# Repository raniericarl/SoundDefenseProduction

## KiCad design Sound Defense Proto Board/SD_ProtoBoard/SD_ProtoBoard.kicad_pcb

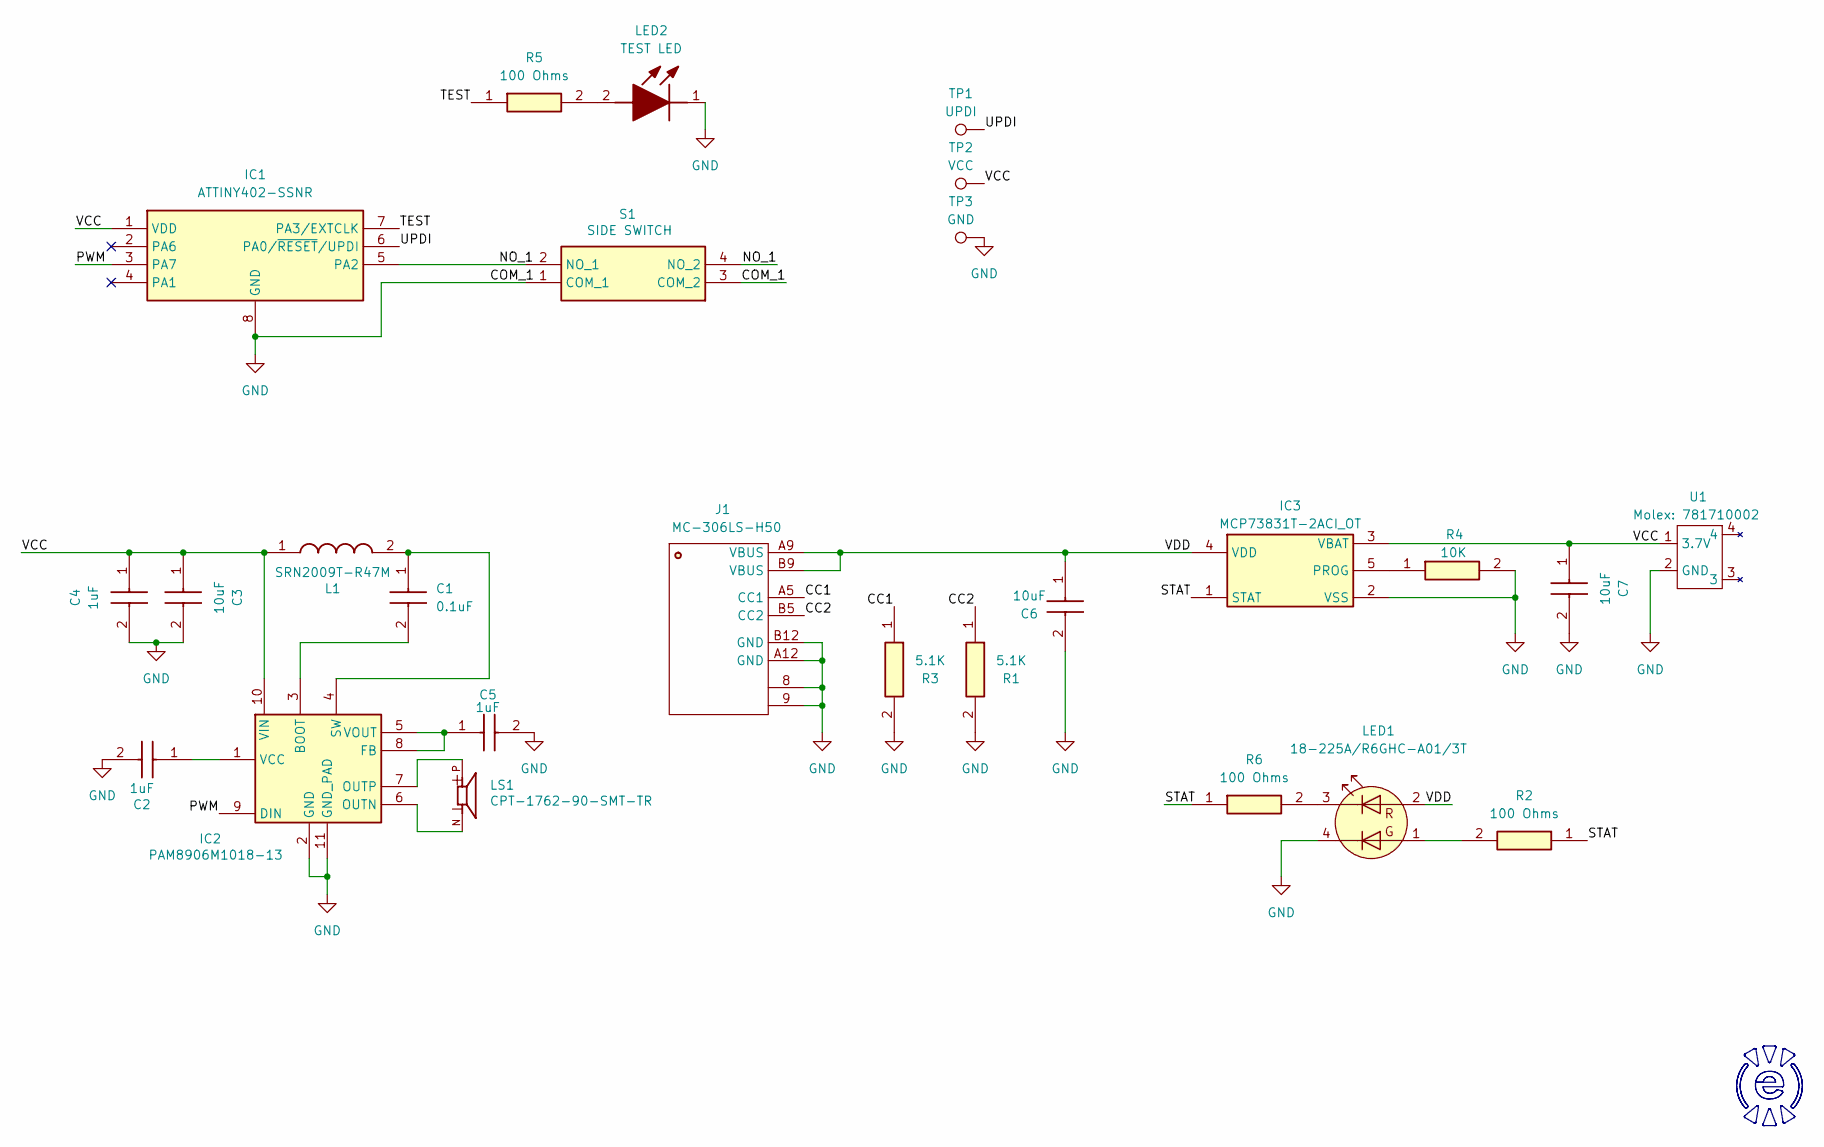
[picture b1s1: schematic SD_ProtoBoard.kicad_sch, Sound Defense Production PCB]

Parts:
C1: 0.1uF; CAPC1005X55N; Manufacturer_Part_Number 0402B104K160CT; Mouser Part Number 791-0402B104K160CT
C2, C4, C5: 1uF; CAPC1005X55N; Manufacturer_Part_Number GRM155R61E105KA12D; Mouser Part Number 81-GRM155R61E105KA2D
C3, C6, C7: 10uF; CAPC1608X90N; Manufacturer_Part_Number GRM188R61E106MA73D; Mouser Part Number 81-GRM188R61E106MA3D
IC1: ATTINY402-SSNR; SOIC127P600X175-8N; Manufacturer_Part_Number ATTINY402-SSNR; Mouser Part Number 579-ATTINY402-SSNR
IC2: PAM8906M1018-13; SOP50P490X110-10N; Manufacturer_Part_Number PAM8906M1018-13; Mouser Part Number 621-PAM8906M1018-13
IC3: MCP73831T-2ACI_OT; SOT95P270X145-5N; Manufacturer_Part_Number MCP73831T-2ACI/OT; Mouser Part Number 579-MCP73831T-2ACIOT
J1: MC-306LS-H50
L1: SRN2009T-R47M; INDC2016X95N; Manufacturer_Part_Number SRN2009T-R47M; Mouser Part Number 652-SRN2009T-R47M
LED1: 18-225A/R6GHC-A01/3T; 18-225A R6GHC-A01 3T
LED2: TEST LED; LEDC1608X80N; Manufacturer_Part_Number 150060VS75000; Mouser Part Number 710-150060VS75000
LS1: CPT-1762-90-SMT-TR; XDCR_CPT-1762-90-SMT-TR; PARTREV 1.01
R1, R3: 5.1K; RESC1005X40N; Manufacturer_Part_Number 0402WGF5101TCE
R2, R5, R6: 100 Ohms; RESC1005X40N; Manufacturer_Part_Number RC0402FR-07100RL; Mouser Part Number 603-RC0402FR-07100RL
R4: 10K; RESC1005X40N; Manufacturer_Part_Number 0402WGF1002TCE
S1: SIDE SWITCH; 436331045822; Manufacturer_Part_Number 436331045822; Mouser Part Number 710-436331045822
TP1: UPDI; TestPoint_Pad_2.5x2.5mm
TP2: VCC; TestPoint_Pad_2.5x2.5mm
TP3: GND; TestPoint_Pad_3.0x3.0mm
U1: Molex: 781710002; CONN02_781710002_MOL

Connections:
/CC1: J1.A5 (CC1), R3.1
/CC2: J1.B5 (CC2), R1.1
/NO_1: IC1.5 (PA2), S1.2 (NO_1), S1.4 (NO_2)
/PWM: IC1.3 (PA7), IC2.9 (DIN)
/STAT: IC3.1 (STAT), R2.1, R6.1
/TEST: IC1.7 (PA3/EXTCLK), R5.1
/UPDI: IC1.6 (PA0/~RESET/UPDI), TP1.1
/VCC: C3.1, C4.1, C7.1, IC1.1 (VDD), IC2.10 (VIN), IC3.3 (VBAT), L1.1, TP2.1, U1.1 (3.7V)
/VDD: C6.1, IC3.4 (VDD), J1.A9 (VBUS), J1.B9 (VBUS), LED1.2 (A1)
GND: C2.2, C3.2, C4.2, C5.2, C6.2, C7.2, IC1.8 (GND), IC2.2 (GND), IC2.11 (GND_PAD), IC3.2 (VSS), J1.8, J1.9, J1.A12 (GND), J1.B12 (GND), LED1.4 (K2), LED2.1 (K), R1.2, R3.2, R4.2, S1.1 (COM_1), S1.3 (COM_2), TP3.1, U1.2 (GND)
unnamed: C1.2, IC2.3 (BOOT)
unnamed: C5.1, IC2.5 (VOUT), IC2.8 (FB)
unnamed: IC2.6 (OUTN), LS1.N
unnamed: IC2.7 (OUTP), LS1.P
unnamed: C1.1, IC2.4 (SW), L1.2
unnamed: C2.1, IC2.1 (VCC)
unnamed: IC3.5 (PROG), R4.1
unnamed: LED1.1 (A2), R2.2
unnamed: LED1.3 (K1), R6.2
unnamed: LED2.2 (A), R5.2

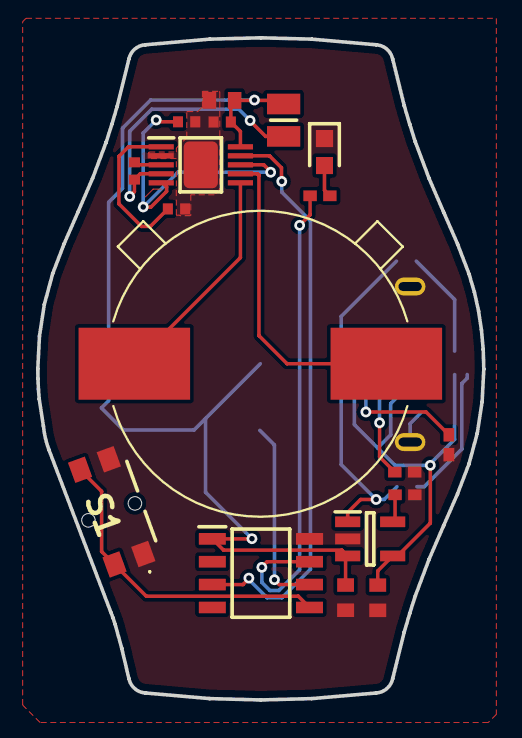
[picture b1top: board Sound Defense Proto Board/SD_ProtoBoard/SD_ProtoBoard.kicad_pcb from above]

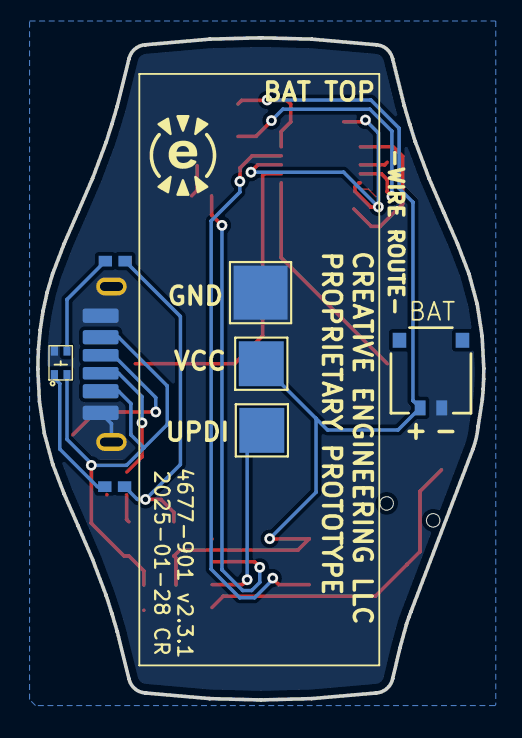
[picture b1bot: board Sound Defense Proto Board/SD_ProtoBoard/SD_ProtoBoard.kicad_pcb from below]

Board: 2 copper layers, 24.8 x 36.8 mm, 26 parts (8 on the bottom side), 20 nets.

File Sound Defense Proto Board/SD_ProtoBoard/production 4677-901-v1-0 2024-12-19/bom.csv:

Designator,Footprint,Quantity,Value,LCSC Part #
C1,CAPC1005X55N,1,0.1uF,
"C2, C4, C5",CAPC1005X55N,3,1uF,
"C3, C6, C7",CAPC1608X90N,3,10uF,
IC1,SOIC127P600X175-8N,1,ATTINY402-SSNR,
IC2,SOP50P490X110-10N,1,PAM8906M1018-13,
IC3,SOT95P270X145-5N,1,MCP73831T-2ACI_OT,
J1,MC-306LS-H50,1,MC-306LS-H50,
L1,INDC2016X95N,1,SRN2009T-R47M,
LED1,LEDC1608X80N,1,CHARGE INDICATOR,
LS1,XDCR_CPT-1762-90-SMT-TR,1,CPT-1762-90-SMT-TR,
"R1, R3",RESC1005X40N,2,5.1K,
R2,RESC1005X40N,1,100 Ohms,
R4,RESC1005X40N,1,10K,
S1,436331045822,1,SIDE SWITCH,
TP1,TestPoint_Pad_2.5x2.5mm,1,UPDI,
TP2,TestPoint_Pad_2.5x2.5mm,1,VCC,
TP3,TestPoint_Pad_3.0x3.0mm,1,GND,
U1,LP402025,1,LP401230,

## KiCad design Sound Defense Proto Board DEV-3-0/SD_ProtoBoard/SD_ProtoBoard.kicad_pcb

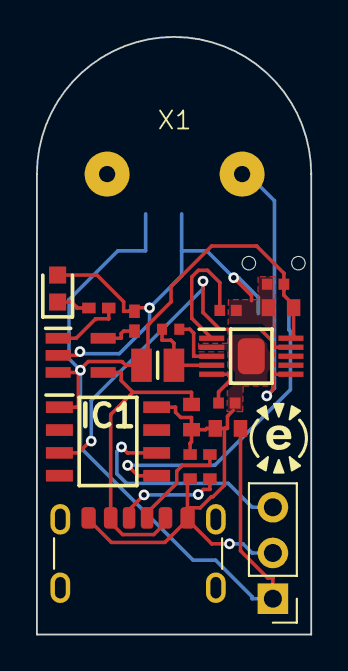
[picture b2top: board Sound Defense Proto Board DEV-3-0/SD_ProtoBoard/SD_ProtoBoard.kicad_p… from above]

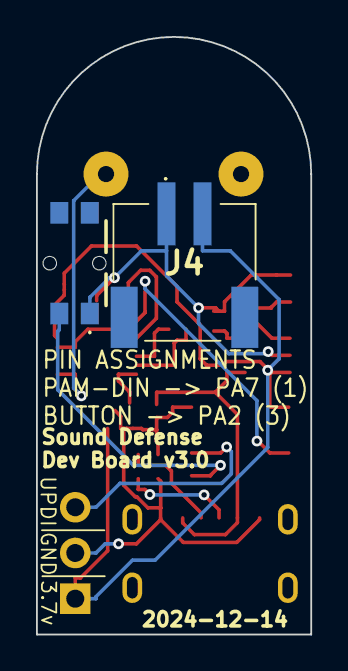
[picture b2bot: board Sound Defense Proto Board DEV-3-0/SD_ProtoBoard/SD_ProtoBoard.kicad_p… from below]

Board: 2 copper layers, 15.2 x 33.2 mm, 21 parts (2 on the bottom side), 17 nets.

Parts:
C1: 0.1uF 0402B104K160CT; CAPC1005X55N
C2, C4, C5: 1uF GRM155R61E105KA12D; CAPC1005X55N
C3, C6, C7: 10uF GRM188R61E106MA73D; CAPC1608X90N
IC1: ATTINY402-SSNR; SOIC127P600X175-8N
IC2: PAM8906M1018-13; SOP50P490X110-10N
IC3: MCP73831T-2ACI_OT; SOT95P270X145-5N
J1: Conn_01x03_Pin; PinHeader_1x03_P2.54mm_Vertical
J3: USB_C_Receptacle_PowerOnly_6P; USB_C_Receptacle_GCT_USB4125-xx-x-0190_6P_TopMnt_Horizontal
J4: S2B-PH-SM4-TB_LF__SN_; S2BPHSM4TBLFSN
L1: SRN2009T-R47M; INDC2016X95N
LED1: 150060VS75000; LEDC1608X80N
R1, R3: 5.1KOhm; RESC1005X40N
R2: 100 Ohms; RESC1005X40N
R4: 10K Ohm; RESC1005X40N
S1: 436331045822
X1: CPT-1404-85T; SD-CPT-1404-85T

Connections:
/UPDI: IC1.6 (PA0/~RESET/UPDI), J1.3
/VBAT: C3.1, C4.1, C7.1, IC1.1 (VDD), IC2.10 (VIN), IC3.3 (VBAT), J1.1, J4.2, L1.1
GND: C2.1, C3.2, C4.2, C5.2, C6.1, C7.2, IC1.8 (GND), IC2.2 (GND), IC2.11 (GND_PAD), IC3.2 (VSS), J1.2, J3.A12 (GND), J3.B12 (GND), J4.1, LED1.2 (A), R1.1, R3.1, R4.2, S1.1 (COM_1)
unnamed: IC1.5 (PA2), S1.2 (NO_1)
unnamed: IC1.3 (PA7), IC2.9 (DIN)
unnamed: C1.2, IC2.3 (BOOT)
unnamed: C2.2, IC2.5 (VOUT), IC2.8 (FB)
unnamed: IC2.6 (OUTN), X1.2
unnamed: IC2.7 (OUTP), X1.1
unnamed: C1.1, IC2.4 (SW), L1.2
unnamed: C5.1, IC2.1 (VCC)
unnamed: IC3.5 (PROG), R4.1
unnamed: IC3.1 (STAT), R2.2
unnamed: C6.2, IC3.4 (VDD), J3.A9 (VBUS), J3.B9 (VBUS)
unnamed: J3.A5 (CC1), R1.2
unnamed: J3.B5 (CC2), R3.2
unnamed: LED1.1 (K), R2.1

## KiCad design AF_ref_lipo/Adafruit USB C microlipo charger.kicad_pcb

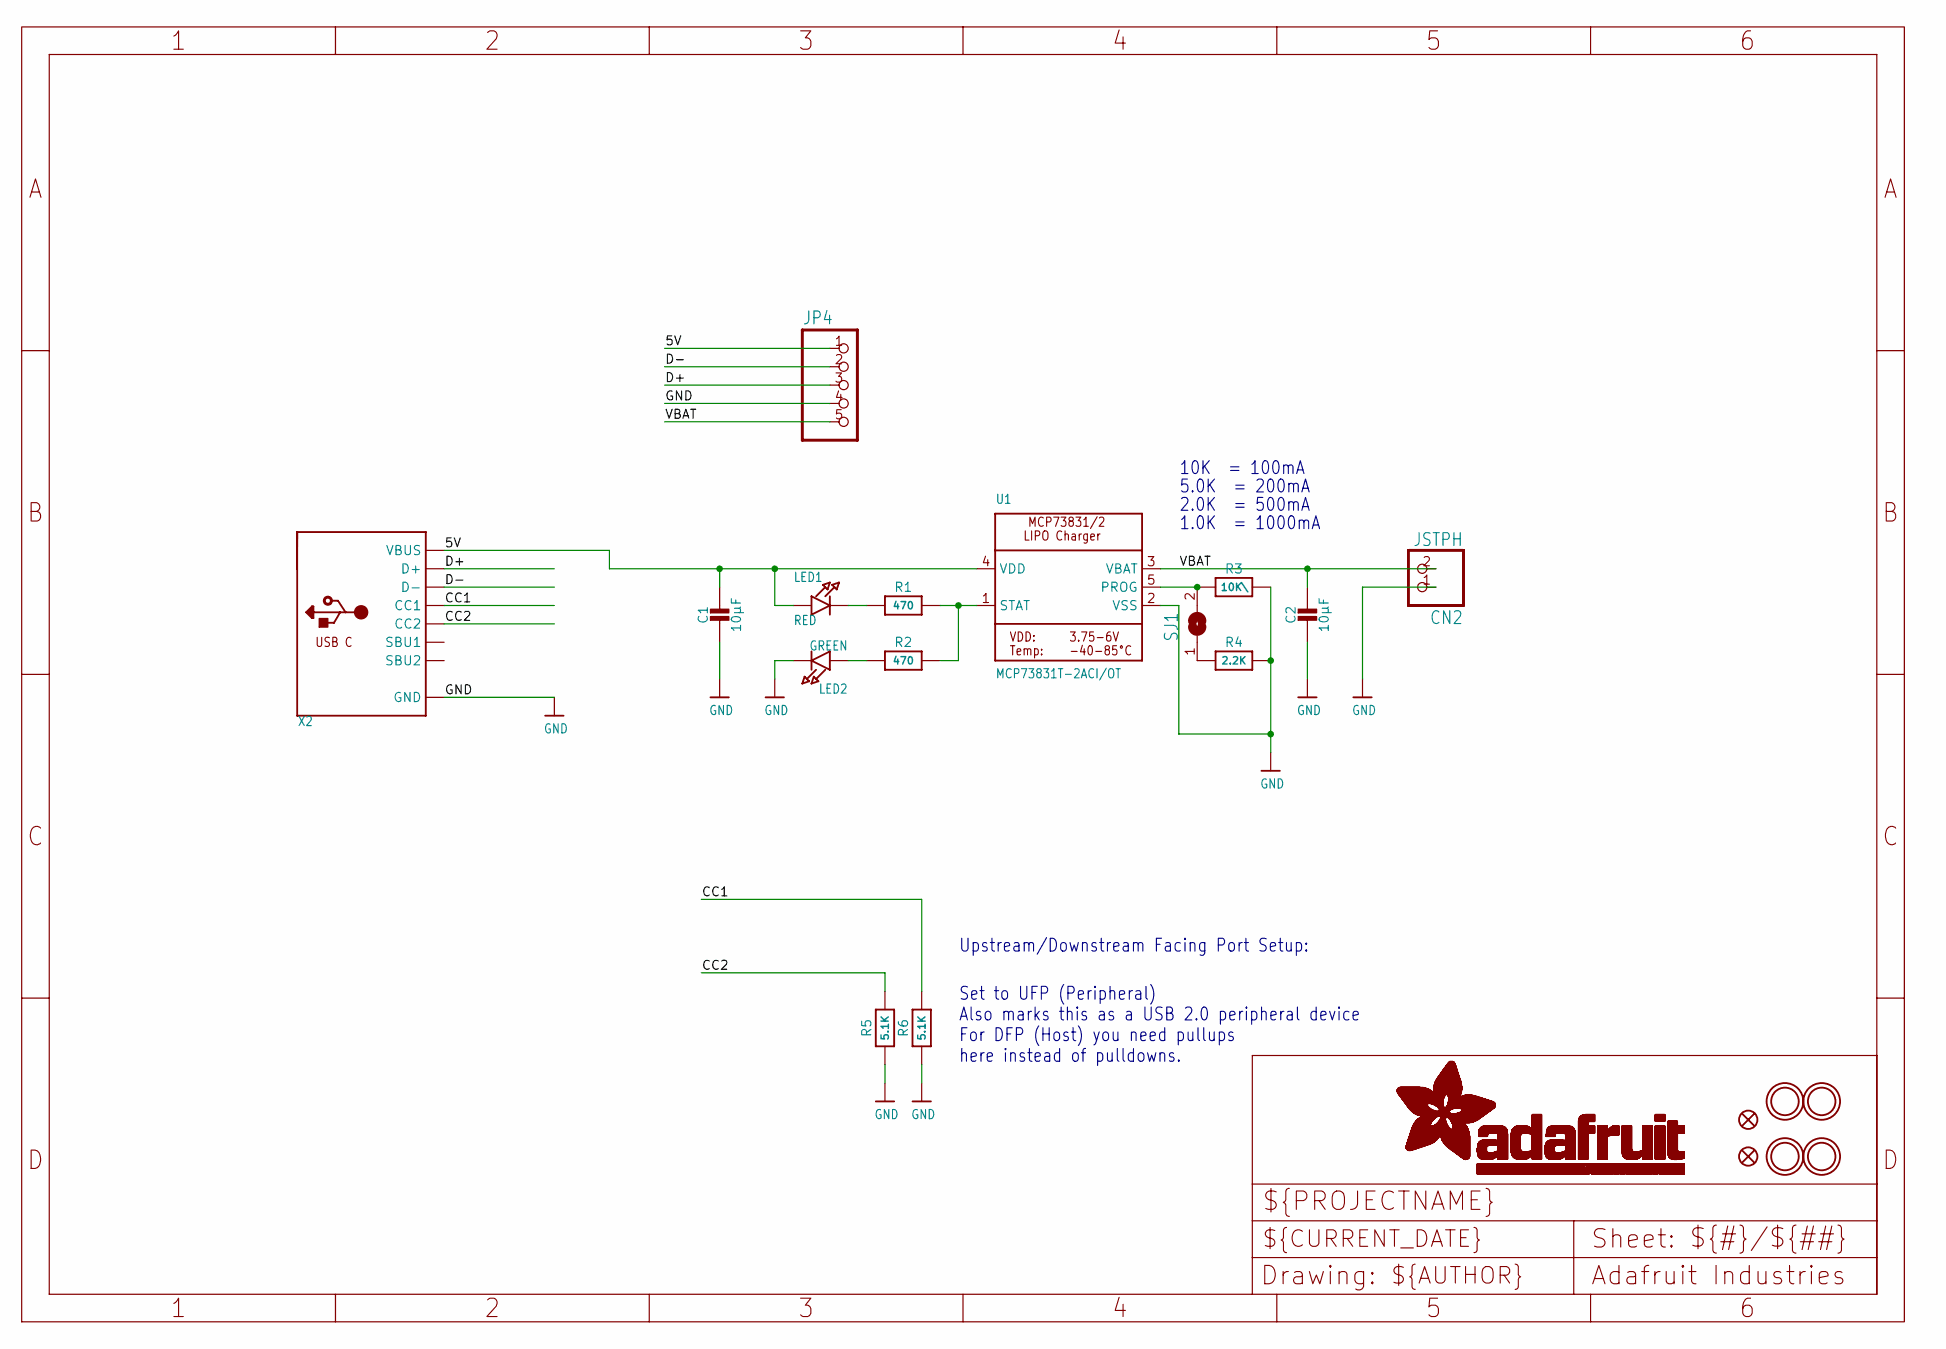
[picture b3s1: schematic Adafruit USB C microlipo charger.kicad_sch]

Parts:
C1, C2: 10µF; 0805-NO@1
CN2: JSTPH; JSTPH2
FID1, FID2: FIDUCIAL""; FIDUCIAL_1MM
JP4: HEADER-1X570MIL; 1X05_ROUND_70
LED1: RED; CHIPLED_0805_NOOUTLINE
LED2: GREEN; CHIPLED_0805_NOOUTLINE
R1, R2: 470; 0603-NO
R3: 10K\; 0603-NO
R4: 2.2K; 0603-NO
R5, R6: 5.1K; 0603-NO
SJ1: SOLDERJUMPER; SOLDERJUMPER_ARROW_NOPASTE
U1: MCP73831T-2ACI/OT; SOT23-5
U$9, U$10, U$11, U$12: MOUNTINGHOLE2.5; MOUNTINGHOLE_2.5_PLATED
X2: USB_C; USB_C_CUSB31-CFM2AX-01-X

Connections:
5V: C1.1, JP4.1, LED1.A, U1.4 (VDD), X2.A4B9 (VBUS), X2.B4A9 (VBUS)
CC1: R6.2, X2.A5 (CC1)
CC2: R5.2, X2.B5 (CC2)
D+: JP4.3, X2.A6 (D+), X2.B6 (D+)
D-: JP4.2, X2.A7 (D-), X2.B7 (D-)
GND: C1.2, C2.2, CN2.1, JP4.4, LED2.C, R3.2, R4.2, R5.1, R6.1, U1.2 (VSS), X2.A1B12 (GND), X2.B1A12 (GND)
unnamed: LED1.C, R1.1
unnamed: R1.2, R2.2, U1.1 (STAT)
unnamed: R4.1, SJ1.1
unnamed: R3.1, SJ1.2, U1.5 (PROG)
unnamed: LED2.A, R2.1
VBAT: C2.1, CN2.2, JP4.5, U1.3 (VBAT)

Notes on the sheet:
1.0K = 1000mA
5.0K = 200mA
Set to UFP (Peripheral) Also marks this as a USB 2.0 peripheral device For DFP (Host) you need pullups here instead of pulldowns.
10K = 100mA
2.0K = 500mA
Upstream/Downstream Facing Port Setup:

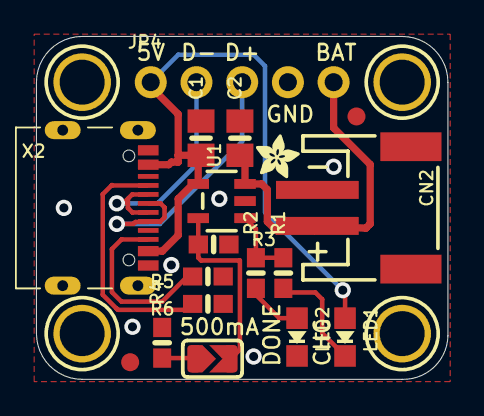
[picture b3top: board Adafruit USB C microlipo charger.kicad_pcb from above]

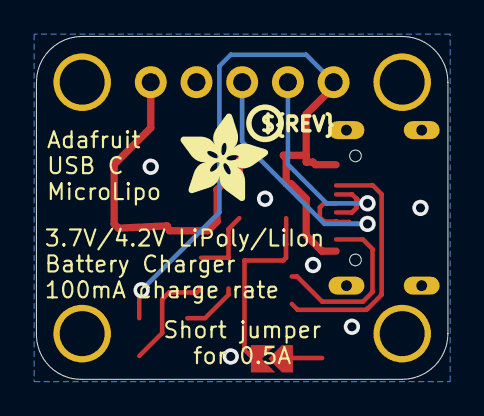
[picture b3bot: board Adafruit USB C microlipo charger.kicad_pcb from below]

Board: 2 copper layers, 22.9 x 19.0 mm, 24 parts (2 on the bottom side), 12 nets.

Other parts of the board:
U$2: ADAFRUIT_2.5MM
U$13: ADAFRUIT_5MM
U$16: PCBFEAT-REV-040

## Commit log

2024-11-15 Initial Project Commit
2024-11-25 Added firmware
2024-12-03 duty cycle
2024-12-06 WakeUp Flag
2024-12-14 New DEV Board and Code
2024-12-24 Production Board v1-0
2024-12-24 Code for hopeful better wakeup
2024-12-30 4677-901 v2.0
